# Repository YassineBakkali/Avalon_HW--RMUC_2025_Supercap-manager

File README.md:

# Avalon - A supercapacitor power manager 

**Avalon** is the custom-designed supercapacitor power manager developed by the **Calibur Robotics team at the National University of Singapore (NUS)** for the **RoboMaster University Championship 2025 (RMUC)**.

This repository contains the full KiCad design files for the Avalon PCB, along with exported schematics and layout PDFs for easier reference and review. Avalon is built to manage high-speed charge and discharge cycles between the robot’s main power source and a dedicated supercapacitor bank.

## Overview

In the RoboMaster competitions, robots must obey strict power limits enforced by the referee system -- typicallycapping the power that can be drawn by the chassis motors at any time. However, short bursts of movement like sprints, collisions, or sudden maneuvers demand far more power than the allowed continuous limit. This creates a mismatch between what the robot can legally draw and what it momentarily needs.

This supercapacitor charger board acts as an intelligent power managemennt module that bridges that gap. By interfacing between the robot's power input (PMM) and supercapacitor bank, it performs real-time charge and discharge cycles to absorb excess power when available and release it when needed. This board thus allow us to perform faster an more agressive movement without breaking power rules.

## How It Works

- During low-power moments (idle, cruise), the board charges the supercaps using leftover headroom from the legal power budget
- When power spikes (e.g. assuming a 24V input, 5A+ with a 60W limit), the board discharges stored energy into the chassis to supplment the robot's main power supply.
- A bidirectional synchronous buck-boost converter, controlled by an STM32G4 microcontroller, enables saemless switching between charge and discharge modes.
- A **high-frequency PID-controlled feedback loop** regulates power transfer at around ~150kHz, ensuring safe and efficient operation.

## Schematics

The full schematics are included as a multi-page PDF [here](pdf/ctl_board.pdf).  
Each sheet is organized by subsystem:

- **Page 1**: Overview / hierarchical design
- **Page 2**: STM32G4 microcontroller and peripherals
- **Page 3**: Power supply regulation, analog references
- **Page 4**: CAN/UART communication interfaces
- **Page 6**: Miscellaneous
- **Page 7**: Main power path and buck-boost gate drivers, current/voltage sensing

Most are clearly labeled, and analog, power, and digital domains are kept well isolated.

## Wiring

The diagram below shows how Avalon is integrated into the robot's power system. It connects between the PMM (referee power module) via J4 and the supercapacitor bank via J15, and communicates with the main control board via CAN. All connectors follow our team's internal wiring standard to ensure compatibility across subsystems.

### Connector Pinout

| Connector | Type       | Function                          |
|-----------|------------|-----------------------------------|
| J4        | XT30PW-M       | Input from PMM                    |
| J15       | XT30PW-F       | Output to supercapacitor bank     |
| J16       | XT30PW-F       | Output to chassis                 |
| J15       | JST GH 4P      | SWD for programming               |
| J8        | JST GH 2P      | CAN(FD)1 communication            |
| J9        | JST GH 2P      | CAN(FD)1 communication            |
| J6        | JST GH 2P      | CAN(FD)3 communication            |
| J7        | JST GH 2P      | CAN(FD)3 communication            |
| J13       | JST GH 4P      | UART4 communication               |
| J14       | JST GH 4P      | UART4 communication               |
| J3        | USB-C          | USB-FS communication              |

## Design choices

This board follows a mixed-signal design, combining high-power switching and analog sensing, so a certain care was taken to physically separate the analog and digital domains. The power section, which includes the buck-boost stage and high-current paths, is isolated from the control logic and signal processing areas to prevent noise from contaminating ADC readings.

*This figure serves as an example of the current sensing circuit used for this board*

To ensure clean current measurements from both the A and B gates of the buck-boost converter as well as the input current, dedicated analog filtering stages were used. Each **INA186** current aplfier is paired with a symmtrical RC filter (100Ω + 10nF) on both inputs, followed by additional bypass capacitors and low-pass filtering before reaching the ADC.

*This figure serves as an example of the voltage sensing circuit used for this board*

In addition to current sensing, voltage measurements (including temperature sensing) are routed through NCS325 OpAmps in a voltage follower configuration (unity gain) with additional RC filtering on both input and output. 

Driving the power stage is an **STM32G474RETx**, chosen specifically for its **HRTIM (High-Resolution Timer)** peripheral. This allows for extremely fine PWM control at high freqencies, which is ideal for safely switching the four NMOS of our buck-boost circuit.
HRTIMs support edad-time insertion and complementary gate control, which are ssential for avoiding shoot-through in the half-bridges and for achieving reliable control at high frequencies.

Connector selection was made with system integration in mind. We stuck to the standard JST GH, and XT30 connectors already used throughout the robot platform. This keeps the board plug-and-play with existing harnesses and avoids unnecessary cable splicing or custom adapters during deployment. 

Thermally, the board is **clearly** overengineered -- 2oz copper on the surface layers, dense thermal via placement, and wie power pours ensure minimal self-heating. In fact, even under sustained 15A+ operation, thermal tests showed satisfactory temperature rise, making on the onboard temperature sesnor effectively redundant. Stil, it's included and routed with the same analog filtering as voltage signals.

## Bill of Materials (BOM)

The BOM was optimized to balance price and availability. Power-side components such as MOSFETs, gate drivers or the STM32 microcontroller were sourced from **Taobao**, while control-side parts like some analog ICs or passives were sourced from **Digi-Key** for better reliability and availability.

A complete list of components (with reference designators and supplier links) can be found in [`bom/ctl_board.csv`](bom/ctl_board.csv).

## Manufacturing Notes

The board was manufactured by JLCPCB, chosen primarily for its affordability and the ability to handle the required specs without compromise. It supports custom stackups, heavier copper layers, and precise drill tolerances at a very reasonable cost, which made it ideal for this project.

For this design, the following fabrication options were used:

- 4-layer PCB stackup using standard RF-4 substrate
- 2 oz copper weight on surface layers to handle high currents and improve thermal performance
- Thermal vias placed around high-power areas and under high-power components (MOSFET gates) to help transfer heat to internal planes
- Blue soldermask, white silkscreen
- ENIG finish (Mostly for bling)

## License

This hardware design is released under the MIT license.  
See [`LICENSE`](LICENSE) for full terms.

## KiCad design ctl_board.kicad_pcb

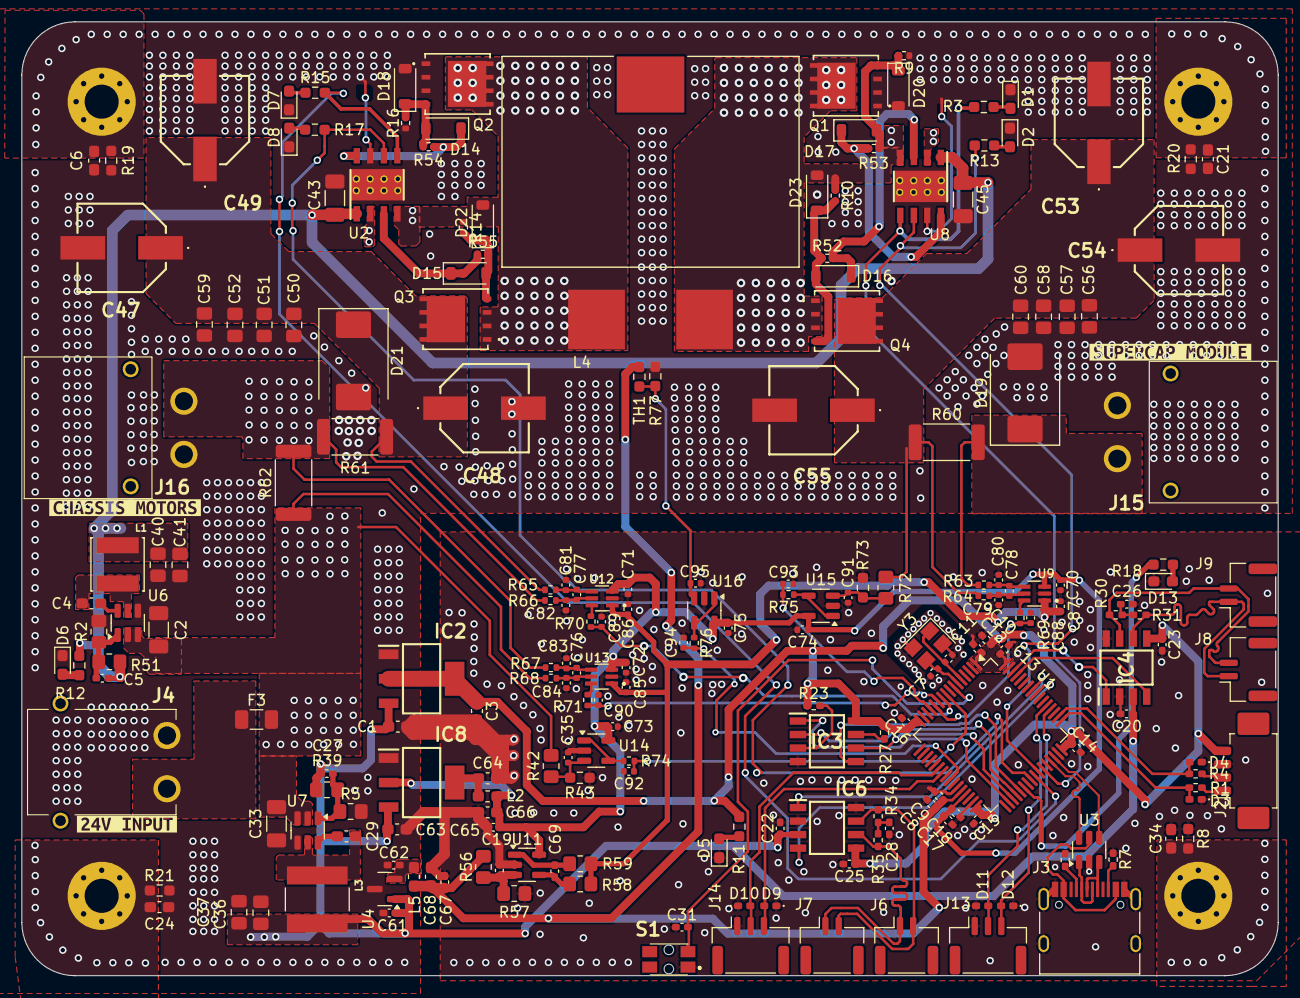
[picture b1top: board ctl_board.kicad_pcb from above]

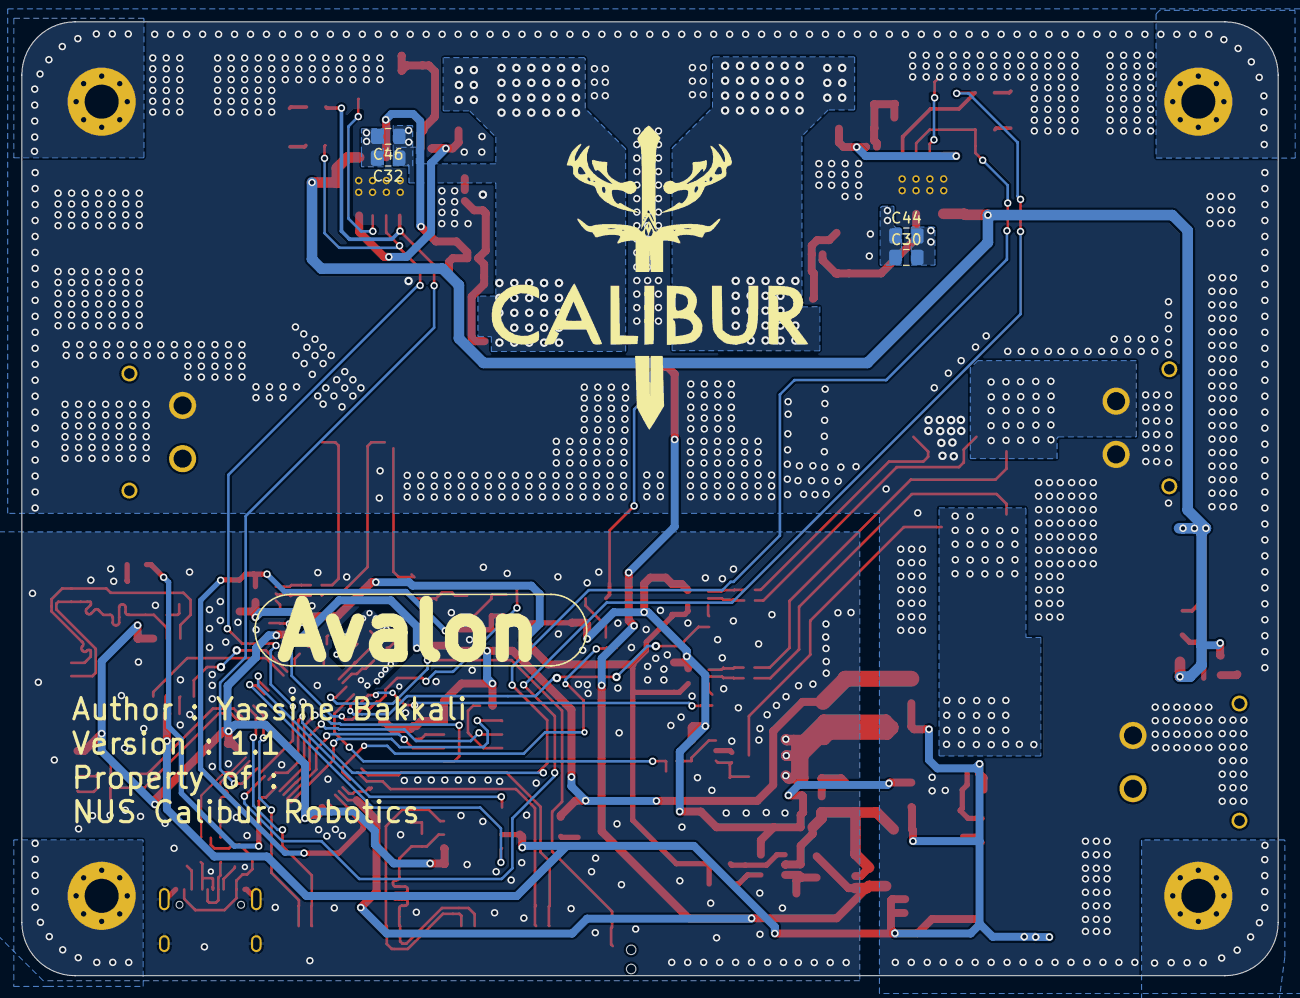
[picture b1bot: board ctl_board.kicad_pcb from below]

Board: 4 copper layers, 118.0 x 89.6 mm, 222 parts (4 on the bottom side), 107 nets.

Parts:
C1, C63, C66, C68: 10uF; C_0603_1608Metric_Pad1.08x0.95mm_HandSolder
C2, C33: 36v10uF; C_1206_3216Metric_Pad1.33x1.80mm_HandSolder
C3, C64: 22uF; C_0603_1608Metric_Pad1.08x0.95mm_HandSolder
C4, C29: 50v100nF; C_0603_1608Metric_Pad1.08x0.95mm_HandSolder
C5, C27: 50v100pF; C_0402_1005Metric_Pad0.74x0.62mm_HandSolder
C6, C21, C24, C34: 1uF; C_0603_1608Metric_Pad1.08x0.95mm_HandSolder
C7, C11: 12pF; C_0402_1005Metric
C8, C12, C13, C14, C15, C16, C19, C20, C22, C23, C25, C31, C61, C62, C65, C67, C69: 100nF; C_0402_1005Metric_Pad0.74x0.62mm_HandSolder
C9, C18: 1uF; C_0402_1005Metric_Pad0.74x0.62mm_HandSolder
C10: 4.7uF; C_0402_1005Metric_Pad0.74x0.62mm_HandSolder
C17: 10nF; C_0402_1005Metric_Pad0.74x0.62mm_HandSolder
C26, C28: 4.7nF; C_0402_1005Metric_Pad0.74x0.62mm_HandSolder
C30, C32: 10uF; C_0805_2012Metric_Pad1.18x1.45mm_HandSolder
C35, C70, C71, C72, C73, C74, C75, C85, C86, C87, C88, C89, C90, C91, C92, C93, C94, C95: 100nF; C_0402_1005Metric
C36, C37, C40, C41: 50v22uF; C_0805_2012Metric_Pad1.18x1.45mm_HandSolder
C43, C45: 10uF; C_1206_3216Metric_Pad1.33x1.80mm_HandSolder
C44, C46: 100nF; C_0805_2012Metric_Pad1.18x1.45mm_HandSolder
C47, C48, C49, C53, C54, C55: 220uF@35V; A769KS227M1VLAS016
C50, C51, C52, C56, C57, C58, C59, C60: 20uF@50V; C_0805_2012Metric_Pad1.18x1.45mm_HandSolder
C76, C77, C78, C79, C80, C81, C82, C83, C84: 10nF; C_0402_1005Metric
D1, D2, D5, D6, D7, D8, D13: LED; LED_0603_1608Metric_Pad1.05x0.95mm_HandSolder
D3, D4, D9, D10, D11, D12: TPD1E10B06DPYR-EV; D_0402_1005Metric_Pad0.77x0.64mm_HandSolder
D14, D15, D16, D17: MMSD4148T3G; D_SOD-123
D18, D20, D22, D23: BAT41ZFILM; D_SOD-123
D19, D21: SMCJ33A; D_SMC
F3: 0685H9300-01; Fuse_1206_3216Metric
H1, H2, H3, H9: MountingHole_Pad; MountingHole_3.2mm_M3_Pad_Via
IC2, IC8: AZ1117CH-3.3TRG1; SOT230P700X180-4N
IC3: AT25EU0021A-SSHN-T; SOIC127P600X175-8N
IC4, IC6: ATA6560-GAQW-N; SOIC127P600X175-8N
J2: MOLEX_ClikMate; Molex_PicoBlade_53261-0471_1x04-1MP_P1.25mm_Horizontal
J3: USB_C_Receptacle_USB2.0; USB_C_Receptacle_HRO_TYPE-C-31-M-12
J4: XT30PW; XT30PWM
J6, J7, J8, J9: JST_GH_SM02; JST_GH_SM02B-GHS-TB_1x02-1MP_P1.25mm_Horizontal
J13, J14: JST_GH_SM03; JST_GH_SM03B-GHS-TB_1x03-1MP_P1.25mm_Horizontal
J15, J16: XT30PW-F; XT30PWF
L1: 10.0uH; IND_VLS5045EX-100M
L2, L5: 26R@100MHz; L_0603_1608Metric_Pad1.05x0.95mm_HandSolder
L3: 3.6uH; IND_ASPI-6045S-3R6N-T
L4: 15uH; IND_SUPERCAP
Q1, Q2, Q3, Q4: POW_NMOS; DFN5&asterisk_6-8L_GFD
R1, R4: 100R; R_0402_1005Metric_Pad0.72x0.64mm_HandSolder
R2, R5: 22.1k; R_0805_2012Metric_Pad1.20x1.40mm_HandSolder
R3, R11, R13, R15, R17, R18: 200R; R_0603_1608Metric_Pad0.98x0.95mm_HandSolder
R6, R7: 5.1kR; R_0402_1005Metric_Pad0.72x0.64mm_HandSolder
R8, R19, R20, R21: 1M; R_0603_1608Metric_Pad0.98x0.95mm_HandSolder
R9, R10, R14, R16: 20k; R_0402_1005Metric
R12: 1k; R_0603_1608Metric_Pad0.98x0.95mm_HandSolder
R23, R27: 4.7k; R_0402_1005Metric_Pad0.72x0.64mm_HandSolder
R30, R31, R34, R35: 60R; R_0402_1005Metric_Pad0.72x0.64mm_HandSolder
R39: 115.8k; R_0805_2012Metric_Pad1.20x1.40mm_HandSolder
R42, R56, R57, R72: 100k; R_0805_2012Metric_Pad1.20x1.40mm_HandSolder
R43, R73, R77: 10k; R_0603_1608Metric_Pad0.98x0.95mm_HandSolder
R51: 309.0k; R_0805_2012Metric_Pad1.20x1.40mm_HandSolder
R52, R53, R54, R55: 1R; R_0402_1005Metric
R58: 1k; R_0805_2012Metric_Pad1.20x1.40mm_HandSolder
R59: 33R; R_0805_2012Metric_Pad1.20x1.40mm_HandSolder
R60, R61, R62: 0.002R; R_2512_6332Metric
R63, R64, R65, R66, R67, R68, R69, R70, R71, R74, R75, R76: 100R; R_0402_1005Metric
S1: EVQP7C01P
TH1: NTC 10K; R_0603_1608Metric_Pad0.98x0.95mm_HandSolder
U1: STM32G474RETx; LQFP-64_10x10mm_P0.5mm
U2, U8: UCC27211AQDDARQ1; DDA0008E_N
U3: USBLC6-2SC6; SOT-23-6
U4: REF3033; SOT-23
U6, U7: AP63200WU; TSOT-23-6
U9, U12, U13: INA186A2IDCKT; INA186
U11, U14, U15, U16: NCS325; SOT-23-5
Y3: ECS-480-8-33B2Q-JVY-TR3; Crystal_SMD_3225-4Pin_3.2x2.5mm
kibuzzard-6681496D: G***; kibuzzard-6681496D
kibuzzard-6681497F: G***; kibuzzard-6681497F
kibuzzard-66814953: G***; kibuzzard-66814953

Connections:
+1V65REF: C85.1, C86.1, C87.1, R58.1, R59.1, U9.1, U12.1, U13.1
+3.3VA: C17.1, C18.1, C65.1, C66.1, C70.1, C71.1, C72.1, C73.1, C74.1, C75.1, IC8.2 (OUTPUT), L2.2, U1.29 (VDDA), U9.3, U11.5 (V+), U12.3, U13.3, U14.5 (V+), U15.5 (V+), U16.5 (V+)
+3.3VREF: C8.1, C9.1, C67.1, C68.1, L5.2, R56.1, TH1.1, U1.28 (VREF+)
+3V3: C3.1, C10.1, C12.1, C13.1, C14.1, C15.1, C16.1, C23.1, C25.1, IC2.2 (OUTPUT), IC2.4 (VOUT), IC3.8 (VCC), IC4.5 (NSIL), IC6.5 (NSIL), J2.4, R11.2, R23.1, R27.2, U1.1 (VBAT), U1.16 (VDD), U1.32 (VDD), U1.48 (VDD), U1.64 (VDD)
+5VD: C1.1, C20.1, C22.1, C27.2, C36.2, C37.2, C61.1, C63.1, IC2.3 (INPUT), IC4.3 (VCC), IC6.3 (VCC), IC8.3 (INPUT), L3.2, R39.1, U4.1 (IN)
+12V: C5.2, C40.2, C41.2, C43.1, C45.1, L1.2, R12.2, R51.1, U2.1 (VDD), U8.1 (VDD)
+24V: C2.1, C33.1, F3.2, R42.2, R62.1, R68.2, U6.2 (EN), U6.3 (IN), U7.2 (EN), U7.3 (IN)
/CAN_UART INTERFACES/CAN1_+: IC4.7 (CANH), J8.2, J9.2, R30.1
/CAN_UART INTERFACES/CAN1_-: IC4.6 (CANL), J8.1, J9.1, R31.2
/CAN_UART INTERFACES/CAN3_+: IC6.7 (CANH), J6.2, J7.2, R34.1
/CAN_UART INTERFACES/CAN3_-: IC6.6 (CANL), J6.1, J7.1, R35.2
/CAN_UART INTERFACES/PB3.FDCAN3_RX: IC6.4 (RXD), U1.56 (PB3)
/CAN_UART INTERFACES/PB4.FDCAN3_TX: IC6.1 (TXD), U1.57 (PB4)
/CAN_UART INTERFACES/PB8.FDCAN1_RX: IC4.4 (RXD), U1.61 (PB8)
/CAN_UART INTERFACES/PB9.FDCAN1_TX: IC4.1 (TXD), U1.62 (PB9)
/CAN_UART INTERFACES/PC4.UART1_TX: D10.2 (K2), J14.2, U1.22 (PC4)
/CAN_UART INTERFACES/PC5.UART1_RX: D9.2 (K2), J14.3, U1.23 (PC5)
/CAN_UART INTERFACES/PC10.UART4_TX: D11.2 (K2), J13.2, U1.52 (PC10)
/CAN_UART INTERFACES/PC11.UART4_RX: D12.2 (K2), J13.3, U1.53 (PC11)
/MCU/PA0.ADC1_IN1|I_CAP_ADC: C88.1, R69.2, U1.12 (PA0)
/MCU/PA1.ADC1_IN2|V_TEMP_ADC: C94.1, R76.2, U1.25 (PB1)
/MCU/PA2.ADC1_IN3|I_CHASSIS_ADC: C90.1, R71.2, U1.11 (PC3)
/MCU/PA9.TIM1_CH3|CAP_MOS_HIGH: R3.2, U1.43 (PA9), U8.5 (HI)
/MCU/PA10.TIM1_CH2|BAT_MOS_HIGH: R15.2, U1.41 (PC9), U2.5 (HI)
/MCU/PA13.SWDIO: D3.2 (K2), R1.2, U1.49 (PA13)
/MCU/PA14.SWCLK: D4.2 (K2), R4.2, U1.50 (PA14)
/MCU/PB0.TIM1_CH2N|BAT_MOS_LOW: R17.2, U1.40 (PC8), U2.6 (LI)
/MCU/PB1.TIM1_CH3N|CAP_MOS_LOW: R13.2, U1.42 (PA8), U8.6 (LI)
/MCU/PB12.SPI2_CS: IC3.1 (~CS), U1.34 (PB12)
/MCU/PB13.SPI2_SCK: IC3.6 (SCK), U1.35 (PB13)
/MCU/PB14.SPI2_MISO: IC3.2 (SO(IO1)), U1.36 (PB14)
/MCU/PB15.SPI2_MOSI: IC3.5 (SI(IO0)), U1.37 (PB15)
/MCU/PC1.ADC2_IN7|V_CHASSIS_ADC: C92.1, R74.2, U1.9 (PC1)
/MCU/PC2.ADC2_IN8|I_SOURCE_ADC: C89.1, R70.2, U1.10 (PC2)
/MCU/PC3.ADC2_IN9|V_CAP_ADC: C93.1, R75.2, U1.13 (PA1)
/MCU/PC8.LED_DRV: R18.2, U1.38 (PC6)
/MCU/PF0.RCC_IN: C11.2, U1.5 (PF0), Y3.1
/MCU/PF1.RCC_OUT: C7.1, U1.6 (PF1), Y3.3
/MCU/PG10.RST: C31.2, S1.2 (COM_1), U1.7 (PG10)
/MCU/USB_DN: U1.45 (PA11), U3.6 (I/O1)
/MCU/USB_DP: U1.46 (PA12), U3.4 (I/O2)
/Super Capacitor Charging Gates/BOOST_DRVH: D16.1 (K), R52.2, U8.3 (HO)
/Super Capacitor Charging Gates/BOOST_DRVL: D17.1 (K), R53.2, U8.8 (LO)
/Super Capacitor Charging Gates/BOOST_SOURCE: C32.1, C46.1, D23.2 (A), L4.2, Q1.1 (D), Q4.3 (S), R10.1, U8.4 (HS)
/Super Capacitor Charging Gates/BUCK_DRVH: D15.1 (K), R55.1, U2.3 (HO)
/Super Capacitor Charging Gates/BUCK_DRVL: D14.1 (K), R54.1, U2.8 (LO)
/Super Capacitor Charging Gates/BUCK_SOURCE: C30.1, C44.1, D22.2 (A), L4.1, Q2.1 (D), Q3.3 (S), R14.1, U2.4 (HS)
/Super Capacitor Charging Gates/CHARGER_IN: C47.1, C48.1, C49.1, C50.1, C51.1, C52.1, C59.1, D21.1 (K), Q3.1 (D), R61.2, R65.1
/Super Capacitor Charging Gates/CHASSIS_OUT: J16.2, R61.1, R62.2, R66.2, R67.1
/Super Capacitor Charging Gates/I_CAP: R69.1, U9.6
/Super Capacitor Charging Gates/I_CHASSIS: R71.1, U13.6
/Super Capacitor Charging Gates/I_SOURCE: R70.1, U12.6
/Super Capacitor Charging Gates/SUPERCAP_CHG: D19.1 (K), J15.2, R60.2, R63.1
/Super Capacitor Charging Gates/SUPERCAP_IN: C53.1, C54.1, C55.1, C56.1, C57.1, C58.1, C60.1, Q4.1 (D), R60.1, R64.2, R72.2
/Super Capacitor Charging Gates/V_CAP: R75.1, U15.1, U15.4 (-)
/Super Capacitor Charging Gates/V_CHASSIS: R74.1, U14.1, U14.4 (-)
/Super Capacitor Charging Gates/V_TEMP: R76.1, U16.1, U16.4 (-)
GND: C1.2, C2.2, C3.2, C6.2, C7.2, C8.2, C9.2, C10.2, C11.1, C12.2, C13.2, C14.2, C15.2, C16.2, C17.2, C18.2, C19.2, C20.2, C21.2, C22.2, C23.2, C24.2, C25.2, C26.2, C28.2, C31.1, C33.2, C34.2, C35.1, C36.1, C37.1, C40.1, C41.1, C43.2, C45.2, C47.2, C48.2, C49.2, C50.2, C51.2, C52.2, C53.2, C54.2, C55.2, C56.2, C57.2, C58.2, C59.2, C60.2, C61.2, C62.2, C63.2, C64.2, C65.2, C66.2, C67.2, C68.2, C70.2, C71.2, C72.2, C73.2, C74.2, C75.2, C79.1, C80.2, C81.2, C82.1, C83.2, C84.1, C85.2, C86.2, C87.2, C88.2, C89.2, C90.2, C91.1, C92.2, C93.2, C94.2, C95.1, D1.1 (K), D2.1 (K), D3.1 (K1), D4.1 (K1), D5.1 (K), D6.1 (K), D7.1 (K), D8.1 (K), D9.1 (K1), D10.1 (K1), D11.1 (K1), D12.1 (K1), D13.1 (K), D18.2 (A), D19.2 (A), D20.2 (A), D21.2 (A), IC2.1 (ADJ/GND), IC3.4 (GND), IC4.2 (GND), IC4.8 (STBY), IC6.2 (GND), IC6.8 (STBY), IC8.1 (ADJ/GND), J2.3, J3.A1 (GND), J3.A12 (GND), J3.B1 (GND), J3.B12 (GND), J3.S1 (SHIELD), J4.2, J13.1, J14.1, J15.1, J16.1, Q1.3 (S), Q2.3 (S), R2.2, R5.2, R6.1, R7.1, R8.1, R9.1, R16.1, R19.1, R20.1, R21.1, R43.1, R57.2, R73.1, R77.1, S1.1 (NO_1), U1.15 (VSS), U1.27 (VSSA), U1.31 (VSS), U1.47 (VSS), U1.63 (VSS), U2.7 (VSS), U2.9 (PAD), U3.2 (GND), U4.3 (GND), U6.4 (GND), U7.4 (GND), U8.7 (VSS), U8.9 (PAD), U9.2, U11.2 (V-), U12.2, U13.2, U14.2 (V-), U15.2 (V-), U16.2 (V-), Y3.2, Y3.4
unnamed: C6.1, H1.1, R19.2
unnamed: C21.1, H2.1, R20.2
unnamed: C24.1, H3.1, R21.2
unnamed: C26.1, R30.2, R31.1
unnamed: C28.1, R34.2, R35.1
unnamed: C34.1, H9.1, R8.2
unnamed: C69.1, R59.2, U11.1
unnamed: C76.1, C84.2, R68.1, U13.5
unnamed: C76.2, C83.1, R67.2, U13.4
unnamed: C77.1, C82.2, R66.1, U12.5
unnamed: C77.2, C81.1, R65.2, U12.4
unnamed: C78.1, C79.2, R64.1, U9.5
unnamed: C78.2, C80.1, R63.2, U9.4
unnamed: D1.2 (A), R3.1
unnamed: D2.2 (A), R13.1
unnamed: D5.2 (A), R11.1
unnamed: D6.2 (A), R12.1
unnamed: D7.2 (A), R15.1
unnamed: D8.2 (A), R17.1
unnamed: D13.2 (A), R18.1
unnamed: D14.2 (A), D18.1 (K), Q2.2 (G), R16.2, R54.2
unnamed: D15.2 (A), D22.1 (K), Q3.2 (G), R14.2, R55.2
unnamed: D16.2 (A), D23.1 (K), Q4.2 (G), R10.2, R52.1
unnamed: D17.2 (A), D20.1 (K), Q1.2 (G), R9.2, R53.1
unnamed: F3.1, J4.1
unnamed: IC3.7 (~HOLD/~RESET(IO3)), R27.1
unnamed: IC3.3 (~WP(IO2)), R23.2
unnamed: C64.1, IC8.4 (VOUT), L2.1
unnamed: J2.1, R1.1
unnamed: J2.2, R4.1
unnamed: J3.A5 (CC1), R6.2
unnamed: J3.B5 (CC2), R7.2
unnamed: J3.A6 (D+), J3.B6 (D+), U3.3 (I/O2)
unnamed: J3.A7 (D-), J3.B7 (D-), U3.1 (I/O1)
unnamed: C30.2, C44.2, U2.2 (HB)
unnamed: J3.A4 (VBUS), J3.A9 (VBUS), J3.B4 (VBUS), J3.B9 (VBUS), U3.5 (VBUS)
unnamed: C62.1, L5.1, U4.2 (OUT)
unnamed: C4.1, U6.6 (BST)
unnamed: C5.1, R2.1, R51.2, U6.1 (FB)
unnamed: C4.2, L1.1, U6.5 (SW)
unnamed: C29.1, U7.6 (BST)
unnamed: C27.1, R5.1, R39.2, U7.1 (FB)
unnamed: C29.2, L3.1, U7.5 (SW)
unnamed: C32.2, C46.2, U8.2 (HB)
unnamed: C19.1, R56.2, R57.1, U11.3 (+)
unnamed: C69.2, R58.2, U11.4 (-)
unnamed: C35.2, R42.1, R43.2, U14.3 (+)
unnamed: C91.2, R72.1, R73.2, U15.3 (+)
unnamed: C95.2, R77.2, TH1.2, U16.3 (+)

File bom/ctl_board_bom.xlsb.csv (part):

Reference,Value,Datasheet,Footprint,Qty,Provider,Link,Individual_price,Total
"C1,C43,C45,C63,C66,C68",10uF,~,-- mixed values --,6,Digikey,https://www.digikey.sg/en/products/detail/samsung-electro-me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 and https://www.digikey.sg/en/products/detail/samsung-electro-me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 and https://www.digikey.sg/en/products/detail/samsung-electro-me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,0.1,0.6
"C2,C33",36v10uF,https://www.digikey.sg/en/products/detail/samsung-electro-me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,Capacitor_SMD:C_1206_3216Metric_Pad1.33x1.80mm_HandSolder,2,Digikey,https://www.digikey.sg/en/products/detail/samsung-electro-me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,0.163,0.326
"C3,C64",22uF,~,Capacitor_SMD:C_0603_1608Metric_Pad1.08x0.95mm_HandSolder,2,Digikey,https://www.digikey.sg/en/products/detail/samsung-electro-me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,0.092,0.184
"C4,C29",50v100nF,https://www.digikey.sg/en/products/detail/samsung-electro-me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,Capacitor_SMD:C_0603_1608Metric_Pad1.08x0.95mm_HandSolder,2,Digikey,https://www.digikey.sg/en/products/detail/samsung-electro-me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,0.05,0.1
"C5,C27",50v100pF,https://www.digikey.sg/en/products/detail/yageo/CC0402KRX7R9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,Capacitor_SMD:C_0402_1005Metric_Pad0.74x0.62mm_HandSolder,2,Digikey,https://www.digikey.sg/en/products/detail/yageo/CC0402KRX7R9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,0.035,0.07
"C6,C21,C24,C34",1000nF,~,Capacitor_SMD:C_0603_1608Metric_Pad1.08x0.95mm_HandSolder,4,Digikey,https://www.digikey.sg/en/products/detail/samsung-electro-me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,0.015,0.06
"C7,C11",12pF,~,Capacitor_SMD:C_0402_1005Metric,2,Digikey,https://www.digikey.sg/en/products/detail/murata-electronics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,0.052,0.104
"C8,C12,C13,C14,C15,C16,C19,C20,C22,C23,C25,C31,C35,C44,C46,C61,C62,C65,C67,C69,C70,C71,C72,C73,C74,C75,C85,C86,C87,C91,C95, C88,C89,C90,C92,C93,C94",100nF,~,-- mixed values --,37,Digikey,https://www.digikey.sg/en/products/detail/murata-electronics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 and https://www.digikey.sg/en/products/detail/yageo/CC0805KRX7R9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,0.0355,1.3135
"C9,C18",1uF,~,Capacitor_SMD:C_0402_1005Metric_Pad0.74x0.62mm_HandSolder,2,Digikey,https://www.digikey.sg/en/products/detail/samsung-electro-me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,0.032,0.064
C10,4.7uF,~,Capacitor_SMD:C_0402_1005Metric_Pad0.74x0.62mm_HandSolder,1,Digikey,https://www.digikey.sg/en/products/detail/samsung-electro-me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,0.12,0.12
"C17,C76,C77,C78,C79,C80,C81,C82,C83,C84",10nF,~,-- mixed values --,10,Digikey,https://www.digikey.sg/en/products/detail/murata-electronics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,0.016,0.16
"C26,C28",4.7nF,~,Capacitor_SMD:C_0402_1005Metric_Pad0.74x0.62mm_HandSolder,2,Digikey,https://www.digikey.sg/en/products/detail/yageo/CC0402KRX7R8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,0.028,0.056
"C36,C37,C40,C41",50v22uF,https://www.digikey.sg/en/products/detail/samsung-electro-me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,Capacitor_SMD:C_0805_2012Metric_Pad1.18x1.45mm_HandSolder,4,Taobao,https://item.taobao.com/item.htm?abbucket=7&id=575257940994&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,0.092,0.368
"C47,C48,C49,C53,C54,C55",220uF@35V,https://www.digikey.sg/en/products/detail/kemet/A769KS227M1V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,footprints:A769KS227M1VLAS016,6,Digikey,https://www.digikey.sg/en/products/detail/kemet/A768KS227M1V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,1.01,6.06
"C50,C51,C52,C56,C57,C58,C59,C60",22uF@50V,https://www.digikey.sg/en/products/detail/tdk-corporation/C2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,Capacitor_SMD:C_0805_2012Metric_Pad1.18x1.45mm_HandSolder,8,Taobao,https://item.taobao.com/item.htm?abbucket=7&id=575257940994&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,0.092,0.736
"D1,D2,D5,D6,D7,D8,D13",LED,~,LED_SMD:LED_0603_1608Metric_Pad1.05x0.95mm_HandSolder,7,Taobao,??? LED 0603,0.1,0.7
"D3,D4,D9,D10,D11,D12",TPD1E10B06DPYR-EV,https://assets.nexperia.com/documents/data-sheet/PESD5V0F1BL.pdf,Diode_SMD:D_0402_1005Metric_Pad0.77x0.64mm_HandSolder,6,Digikey,https://www.digikey.sg/en/products/detail/evvo/TPD1E10B06DPY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,0.114,0.684
"D14,D15,D16,D17",MMSD4148T3G,https://www.digikey.sg/en/products/detail/onsemi/MMSD4148T3G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,Diode_SMD:D_SOD-123,4,Digikey,https://www.digikey.sg/en/products/detail/onsemi/MMSD4148T3G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,0.079,0.316
"D18,D20",BAT41ZFILM,"https://item.taobao.com/item.htm?abbucket=7&id=843058445220&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""aplus_abtest""%3A""3272030d4190d25e91d9f1702e97b464""%7D&xxc=taobaoSearch",Diode_SMD:D_SOD-123,2,Taobao,"https://item.taobao.com/item.htm?abbucket=7&id=843058445220&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""aplus_abtest""%3A""3272030d4190d25e91d9f1702e97b464""%7D&xxc=taobaoSearch",0.059,0.118
"D19,D21",SMCJ33A,"https://item.taobao.com/item.htm?abbucket=7&id=586226087667&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""aplus_abtest""%3A""734d230ddad645d330e1175e50131bf3""%7D&xxc=taobaoSearch",Diode_SMD:D_SMC,2,Taobao,,0.055,0.11
F3,0685H9300-01,https://www.digikey.sg/en/products/detail/bel-fuse-inc/0685H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,Fuse:Fuse_1206_3216Metric,1,Digikey,https://www.digikey.sg/en/products/detail/bel-fuse-inc/0685H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,0.52,0.52
"H1,H2,H3,H9",MountingHole_Pad,~,MountingHole:MountingHole_3.2mm_M3_Pad_Via,4,,,0,0
"IC2,IC8",AZ1117CH-3.3TRG1,https://datasheet.datasheetarchive.com/originals/distributor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,SamacSys_Parts:SOT230P700X180-4N,2,Digikey,https://www.digikey.sg/en/products/detail/diodes-incorporate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,0.63,1.26
IC3,AT25EU0021A-SSHN-T,https://www.renesas.com/us/en/products/memory-logic/non-vola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,SOIC127P600X175-8N,1,Digikey,https://www.digikey.sg/en/products/detail/renesas-electronic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,0.52,0.52
"IC4,IC6",ATA6560-GAQW-N,,SamacSys_Parts:SOIC127P600X175-8N,2,Digikey,https://www.digikey.sg/en/products/detail/microchip-technolo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,0.7,1.4
J2,MOLEX_ClikMate,~,Connector_Molex:Molex_CLIK-Mate_502386-0470_1x04-1MP_P1.25mm_Horizontal,1,Taobao,https://item.taobao.com/item.htm?abbucket=7&id=712964987051&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,0.22,0.22
J3,USB_C_Receptacle_USB2.0,https://www.usb.org/sites/default/files/documents/usb_type-c.zip,Connector_USB:USB_C_Receptacle_HRO_TYPE-C-31-M-12,1,Taobao,https://item.taobao.com/item.htm?_u=k20gsmhvnvde93&id=737614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,0.092,0.092
J4,XT30PW,https://www.tme.eu/Document/4acc913878197f8c2e30d4b8cdc47230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,SamacSys_Parts:XT30PWM,1,Taobao,,0,0
"J6,J7,J8,J9",JST_GH_SM02,~,Connector_JST:JST_GH_SM02B-GHS-TB_1x02-1MP_P1.25mm_Horizontal,4,Taobao,https://item.taobao.com/item.htm?_u=k20gsmhvnve153&id=797176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,0.046,0.184
"J13,J14",JST_GH_SM03,~,Connector_JST:JST_GH_SM03B-GHS-TB_1x03-1MP_P1.25mm_Horizontal,2,Taobao,https://item.taobao.com/item.htm?abbucket=7&id=541689461063&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,0.064,0.128
"J15,J16",XT30PW-F,https://www.tme.eu/Document/ce4077e36b79046da520ca73227e15de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,SamacSys_Parts:XT30PWF,2,Taobao,,0,0
L1,10.0uH,https://www.digikey.sg/en/products/detail/tdk-corporation/VL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,footprints:IND_VLS5045EX-100M,1,Digikey,https://www.digikey.sg/en/products/detail/tdk-corporation/VL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,0.47,0.47
"L2,L5",26R@100MHz,https://www.digikey.sg/en/products/detail/murata-electronics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,Inductor_SMD:L_0603_1608Metric_Pad1.05x0.95mm_HandSolder,2,Digikey,https://www.digikey.sg/en/products/detail/murata-electronics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,0.09,0.18
L3,3.6uH,https://www.digikey.sg/en/products/detail/taiyo-yuden/LSXNH8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,footprints:IND_ASPI-6045S-3R6N-T,1,Digikey,https://www.digikey.sg/en/products/detail/taiyo-yuden/LSXNH8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,0.57,0.57
L4,15uH,https://www.bourns.com/docs/Product-Datasheets/PQ2617.pdf,footprints:IND_SUPERCAP,1,Taobao,https://item.taobao.com/item.htm?from=cart&id=693711767751&s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,5.23,5.23
"Q1,Q2,Q3,Q4",POW_NMOS | GT110N06D5 DFN5X6,https://item.taobao.com/item.htm?spm=a1z09.2.0.0.31932e8dp2R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,footprints:DFN5&asterisk_6-8L_GFD,4,,,0.37,1.48
"R1,R4,R63,R64,R65,R66,R67,R68,R69,R70,R71,R74,R75,R76",100R,~,Resistor_SMD:R_0402_1005Metric_Pad0.72x0.64mm_HandSolder,14,Digikey,https://www.digikey.sg/en/products/detail/panasonic-electron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,0.013,0.182
"R2,R5",22.1k,https://www.digikey.sg/en/products/detail/stackpole-electron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,Resistor_SMD:R_0805_2012Metric_Pad1.20x1.40mm_HandSolder,2,Digikey,https://www.digikey.sg/en/products/detail/stackpole-electron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,0.036,0.072
"R3,R12,R13,R15,R17,R58",1k,~,-- mixed values --,6,Digikey,https://www.digikey.sg/en/products/detail/yageo/RC0603FR-071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 and,0.017,0.102
"R6,R7",5.1kR,~,Resistor_SMD:R_0402_1005Metric_Pad0.72x0.64mm_HandSolder,2,Digikey,https://www.digikey.sg/en/products/detail/panasonic-electron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,0.038,0.076
"R8,R19,R20,R21",1M,~,Resistor_SMD:R_0603_1608Metric_Pad0.98x0.95mm_HandSolder,4,Digikey,https://www.digikey.sg/en/products/detail/yageo/RC0603FR-071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,0.013,0.052
"R43,R73,R77",10k,~,Resistor_SMD:R_0603_1608Metric_Pad0.98x0.95mm_HandSolder,3,Digikey,https://www.digikey.sg/en/products/detail/stackpole-electron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,0.028,0.084
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
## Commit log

2025-04-23 Repo setup
2025-04-23 Renamed files, threw out garbage
